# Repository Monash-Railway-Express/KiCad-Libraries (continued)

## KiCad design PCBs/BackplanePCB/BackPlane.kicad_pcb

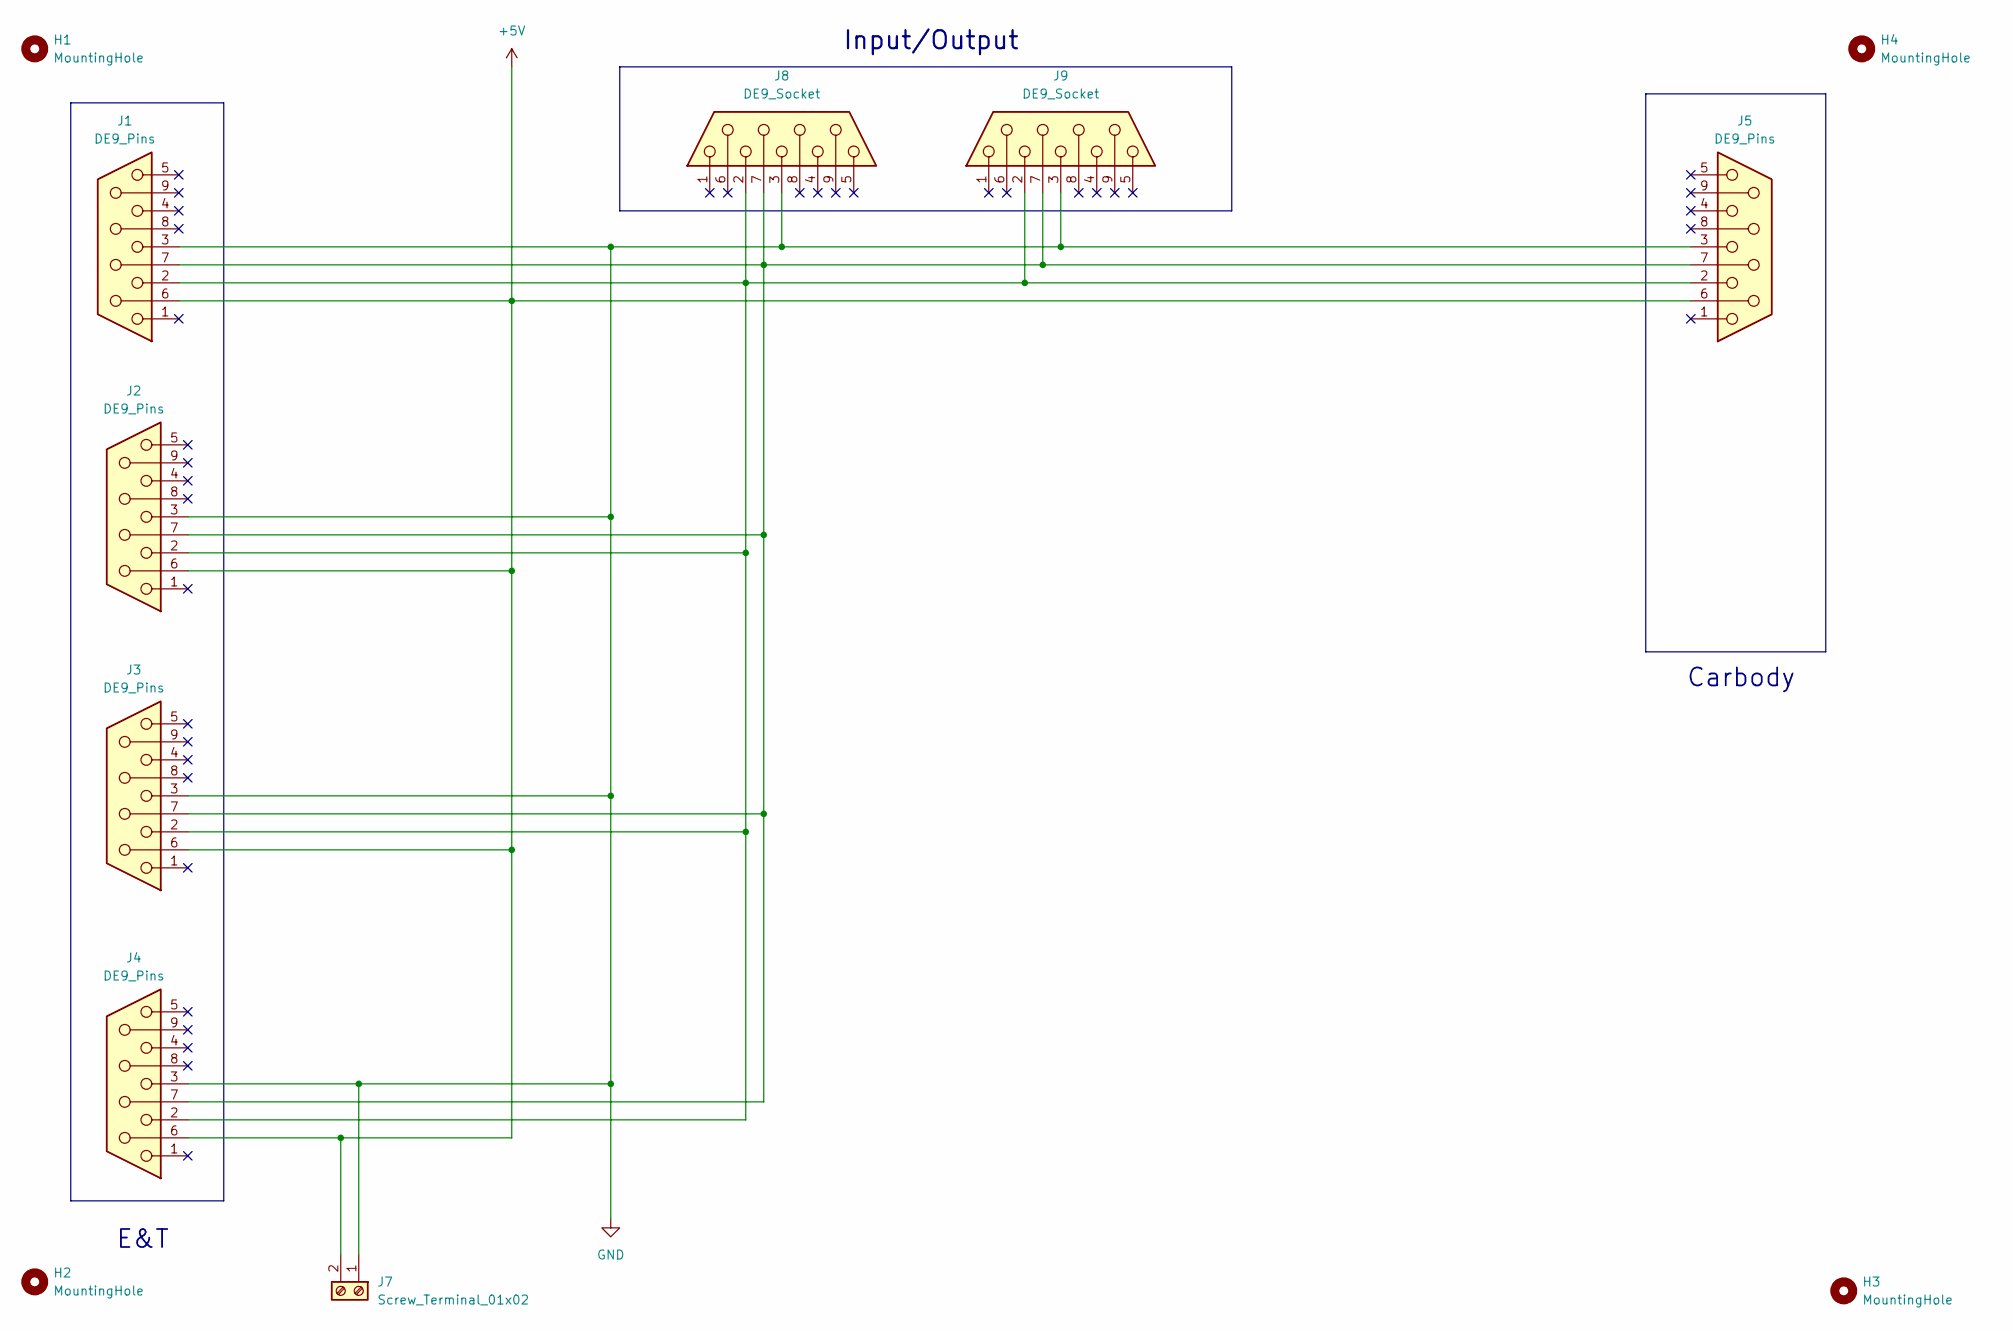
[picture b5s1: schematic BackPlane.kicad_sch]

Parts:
H1, H2, H3, H4: MountingHole; MountingHole_5.3mm_M5_ISO14580
J1, J2, J3, J4, J5: DE9_Pins; DSUB-9_Socket_Vertical_P2.77x2.84mm_MountingHoles
J7: Screw_Terminal_01x02; TerminalBlock_TE_282834-2_1x02_P2.54mm_Horizontal
J8, J9: DE9_Socket; CONN_2301844-1_TEC

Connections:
+5V: J1.6, J2.6, J3.6, J4.6, J5.6, J7.2
GND: J1.3, J2.3, J3.3, J4.3, J5.3, J7.1, J8.3, J9.3
unnamed: J1.2, J2.2, J3.2, J4.2, J5.2, J8.2, J9.2
unnamed: J1.7, J2.7, J3.7, J4.7, J5.7, J8.7, J9.7

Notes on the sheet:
Input/Output
E&T
Carbody

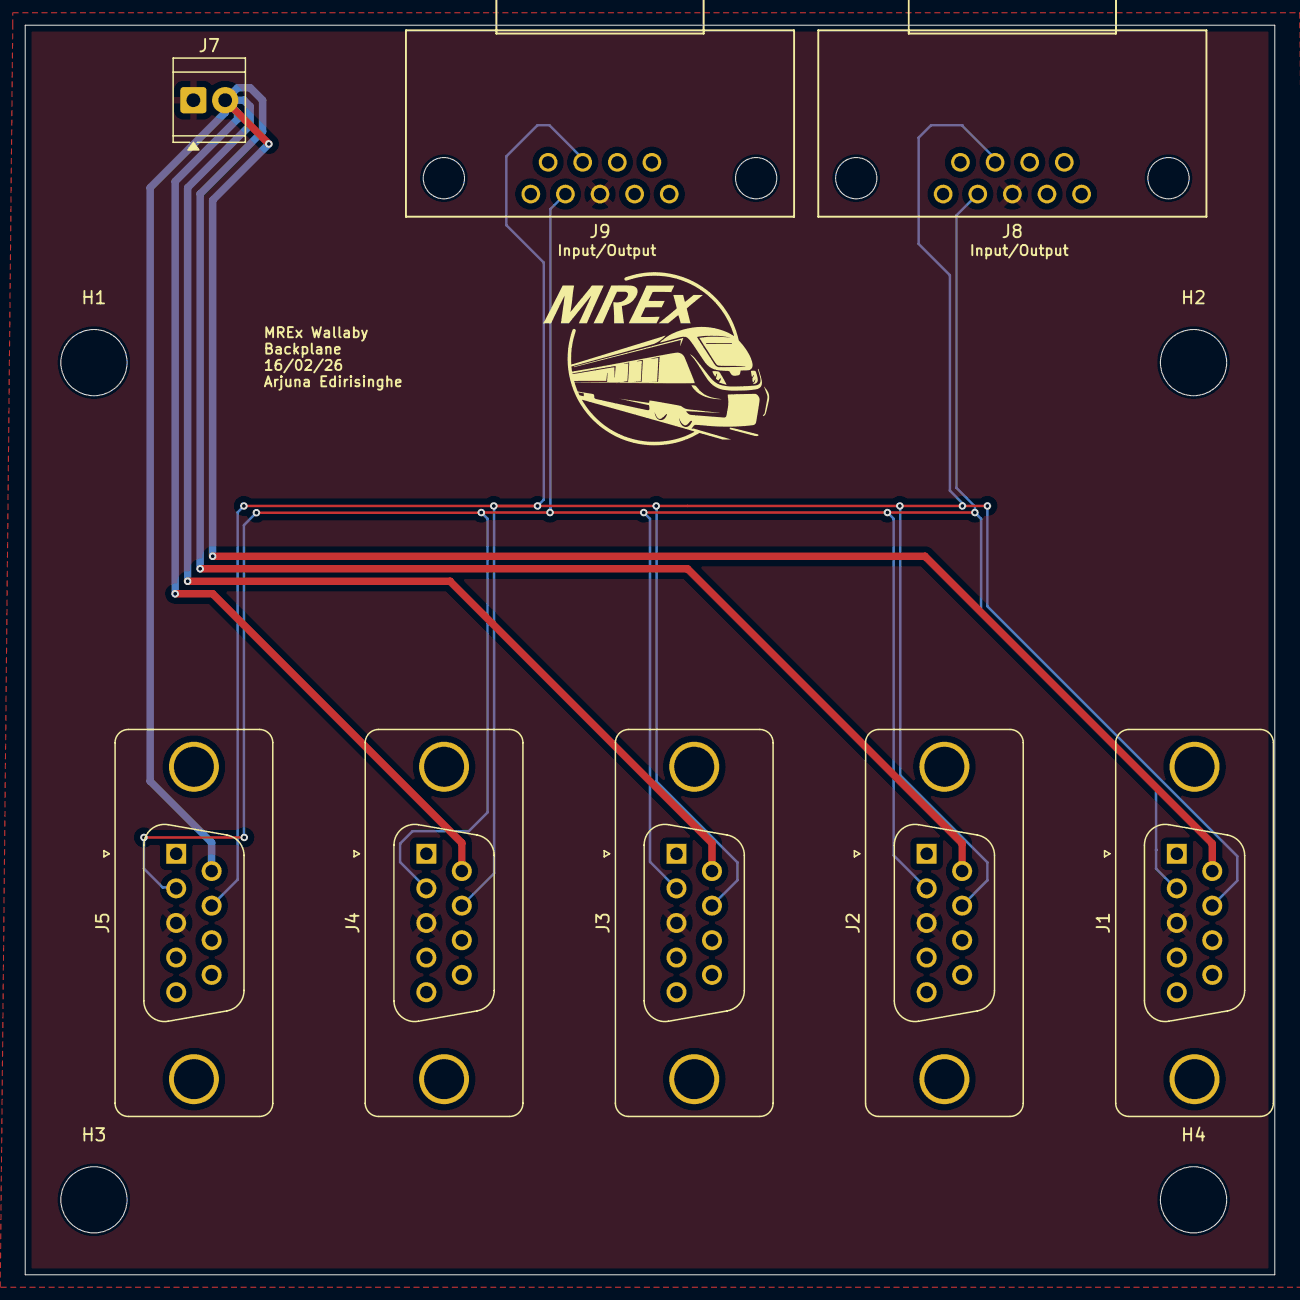
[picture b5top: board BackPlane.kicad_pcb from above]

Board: 2 copper layers, 100.0 x 100.0 mm, 12 parts (0 on the bottom side), 4 nets.

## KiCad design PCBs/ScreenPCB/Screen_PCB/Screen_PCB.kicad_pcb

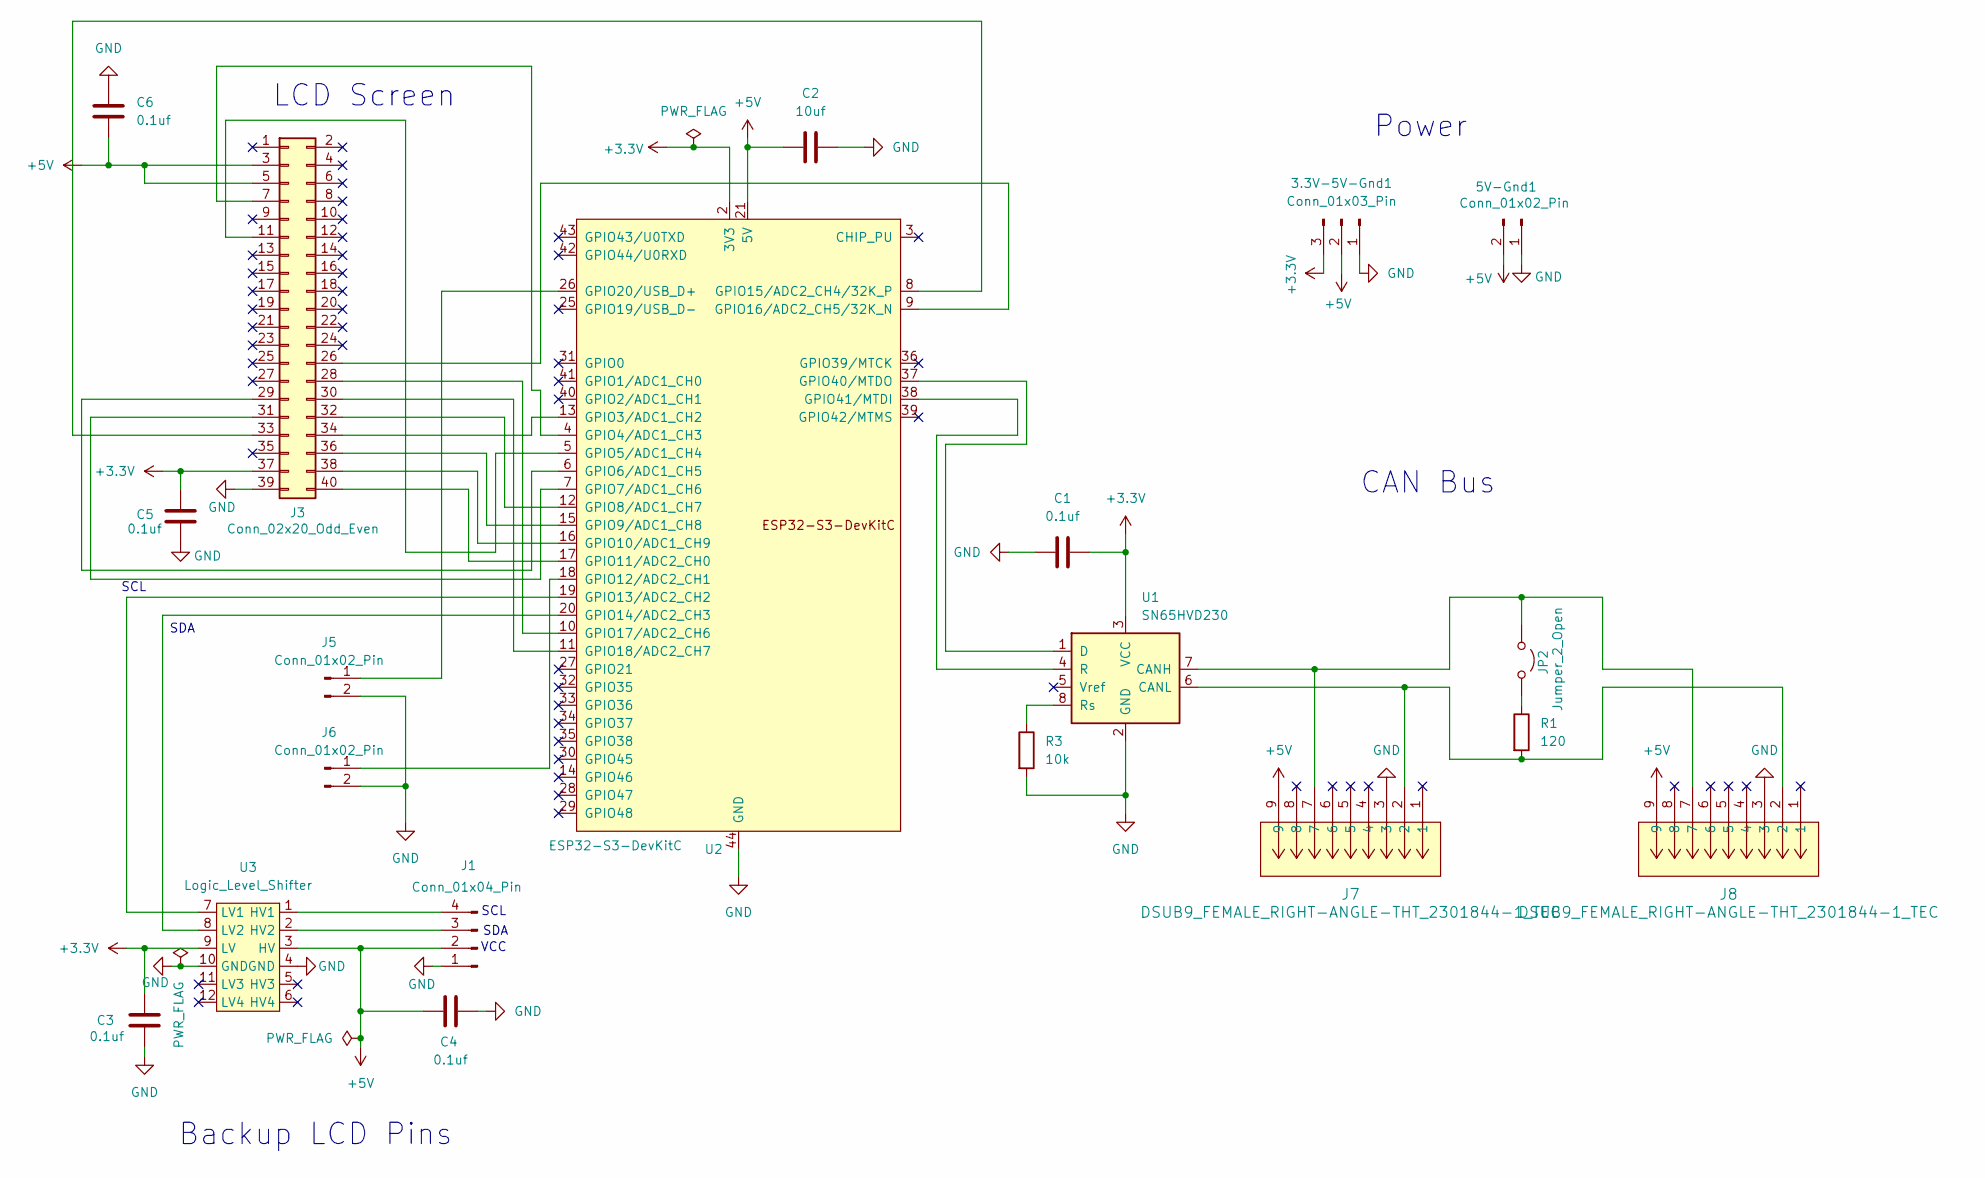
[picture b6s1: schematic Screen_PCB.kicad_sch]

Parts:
3.3V-5V-Gnd1: Conn_01x03_Pin; PinHeader_1x03_P2.54mm_Vertical
5V-Gnd1: Conn_01x02_Pin; PinHeader_1x02_P2.54mm_Vertical
C1, C3, C4, C5, C6: 0.1uf; C_0805_2012Metric
C2: 10uf; C_0805_2012Metric
J1: Conn_01x04_Pin; PinHeader_1x04_P2.54mm_Horizontal
J3: Conn_02x20_Odd_Even; IDC-Header_2x20_P2.54mm_Vertical
J5, J6: Conn_01x02_Pin; PinHeader_1x02_P2.54mm_Horizontal
J7, J8: DSUB9_FEMALE_RIGHT-ANGLE-THT_2301844-1_TEC
JP2: Jumper_2_Open; PinHeader_1x02_P2.54mm_Vertical
R1: 120; R_Axial_DIN0207_L6.3mm_D2.5mm_P7.62mm_Horizontal
R3: 10k; R_Axial_DIN0207_L6.3mm_D2.5mm_P7.62mm_Horizontal
U1: SN65HVD230; SOIC-8_3.9x4.9mm_P1.27mm
U2: ESP32-S3-DevKitC
U3: Logic_Level_Shifter; I2C_Logic_Shifter

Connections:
+3.3V: 3.3V-5V-Gnd1.3, C1.2, C3.1, C5.2, J3.37, U1.3 (VCC), U2.1 (3V3), U2.2 (3V3), U3.9 (LV); also elsewhere on the board
+5V: 3.3V-5V-Gnd1.2, 5V-Gnd1.2, C2.2, C4.1, C6.2, J1.2, J3.3, J3.5, J7.9, J8.9, U2.21 (5V), U3.3 (HV); also elsewhere on the board
GND: 3.3V-5V-Gnd1.1, 5V-Gnd1.1, C1.1, C2.1, C3.2, C4.2, C5.1, C6.1, J1.1, J3.39, J5.2, J6.2, J7.3, J8.3, R3.2, U1.2 (GND), U2.22 (GND), U2.23 (GND), U2.24 (GND), U2.44 (GND), U3.4 (GND), U3.10 (GND); also elsewhere on the board
unnamed: J1.3, U3.2 (HV2)
unnamed: J1.4, U3.1 (HV1)
unnamed: J3.7, U2.4 (GPIO4/ADC1_CH3)
unnamed: J3.11, U2.5 (GPIO5/ADC1_CH4)
unnamed: J3.26, U2.9 (GPIO16/ADC2_CH5/32K_N)
unnamed: J3.28, U2.10 (GPIO17/ADC2_CH6)
unnamed: J3.29, U2.6 (GPIO6/ADC1_CH5)
unnamed: J3.30, U2.11 (GPIO18/ADC2_CH7)
unnamed: J3.31, U2.7 (GPIO7/ADC1_CH6)
unnamed: J3.32, U2.12 (GPIO8/ADC1_CH7)
unnamed: J3.33, U2.8 (GPIO15/ADC2_CH4/32K_P)
unnamed: J3.34, U2.13 (GPIO3/ADC1_CH2)
unnamed: J3.36, U2.15 (GPIO9/ADC1_CH8)
unnamed: J3.38, U2.16 (GPIO10/ADC1_CH9)
unnamed: J3.40, U2.17 (GPIO11/ADC2_CH0)
unnamed: J5.1, U2.26 (GPIO20/USB_D+)
unnamed: J6.1, U2.18 (GPIO12/ADC2_CH1)
unnamed: J7.7, J8.7, JP2.1 (A), U1.7 (CANH)
unnamed: JP2.2 (B), R1.1
unnamed: J7.2, J8.2, R1.2, U1.6 (CANL)
unnamed: U1.1 (D), U2.37 (GPIO40/MTDO)
unnamed: U1.4 (R), U2.38 (GPIO41/MTDI)
unnamed: R3.1, U1.8 (Rs)
unnamed: U2.19 (GPIO13/ADC2_CH2), U3.7 (LV1)
unnamed: U2.20 (GPIO14/ADC2_CH3), U3.8 (LV2)

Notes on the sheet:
SCL
Power
LCD Screen
SDA
VCC
SDA
CAN Bus
SCL
Backup LCD Pins

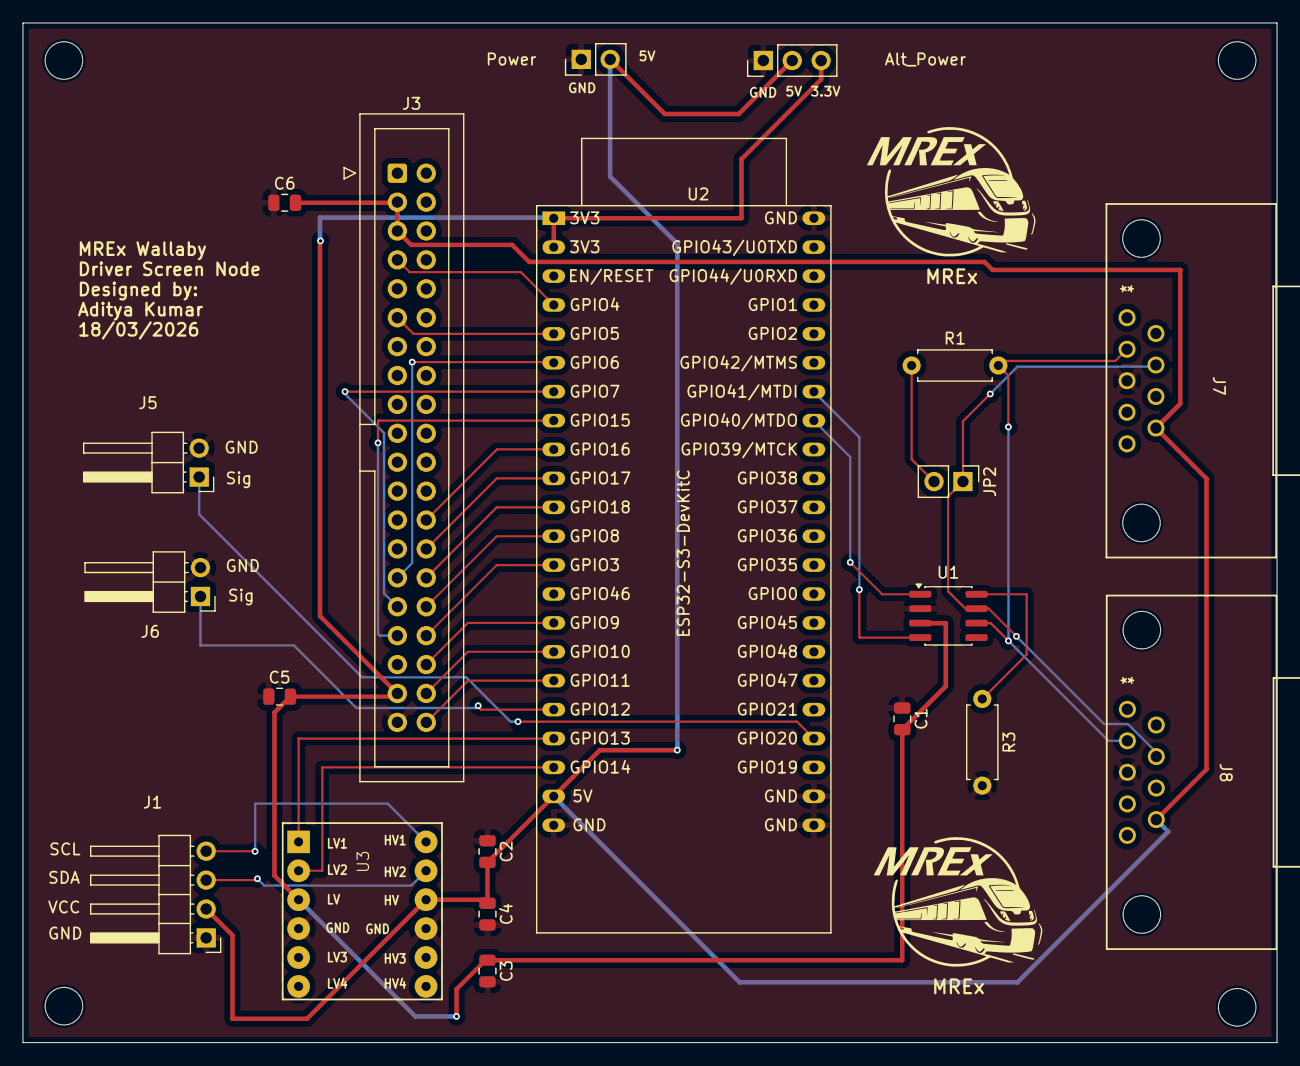
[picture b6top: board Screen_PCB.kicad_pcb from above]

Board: 2 copper layers, 110.2 x 89.6 mm, 22 parts (0 on the bottom side), 28 nets.

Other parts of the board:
Alt_Power: Conn_01x03_Pin; PinHeader_1x03_P2.54mm_Vertical
MREx: LOGO
MREx#2: LOGO
Power: Conn_01x02_Pin; PinHeader_1x02_P2.54mm_Vertical

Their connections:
+3.3V: Alt_Power.3; also elsewhere on the board
+5V: Alt_Power.2, Power.2; also elsewhere on the board
GND: Alt_Power.1, Power.1; also elsewhere on the board

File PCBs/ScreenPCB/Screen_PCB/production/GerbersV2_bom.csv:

Designator,Footprint,Quantity,Value,LCSC Part #
"_4, _3, _2, ",,4,,
BACKUP_SCREEN,PinHeader_1x04_P2.54mm_Horizontal,1,Conn_01x04_Pin,
"C1, C3, C4, C5, C6",0805,5,0.1uf,
C2,0805,1,10uf,
GND-5V,PinHeader_1x02_P2.54mm_Vertical,1,Conn_01x02_Pin,
GND-5V-3.3V,PinHeader_1x03_P2.54mm_Vertical,1,Conn_01x03_Pin,
J3,IDC-Header_2x20_P2.54mm_Vertical,1,Conn_02x20_Odd_Even,
"J7, J8",DSUB9_FEMALE_RIGHT-ANGLE-THT_2301844-1_TEC,2,DSUB9_FEMALE_RIGHT-ANGLE-THT_2301844-1_TEC,
JP2,PinHeader_1x02_P2.54mm_Vertical,1,Jumper_2_Open,
"PUSH_1, PUSH_2",PinHeader_1x02_P2.54mm_Horizontal,2,Conn_01x02_Pin,
R1,R_Axial_DIN0207_L6.3mm_D2.5mm_P7.62mm_Horizontal,1,120,
R3,R_Axial_DIN0207_L6.3mm_D2.5mm_P7.62mm_Horizontal,1,10k,
U1,SOIC-8_3.9x4.9mm_P1.27mm,1,SN65HVD230,
U2,ESP32-S3-DevKitC,1,ESP32-S3-DevKitC,
U3,I2C_Logic_Shifter,1,Logic_Level_Shifter,

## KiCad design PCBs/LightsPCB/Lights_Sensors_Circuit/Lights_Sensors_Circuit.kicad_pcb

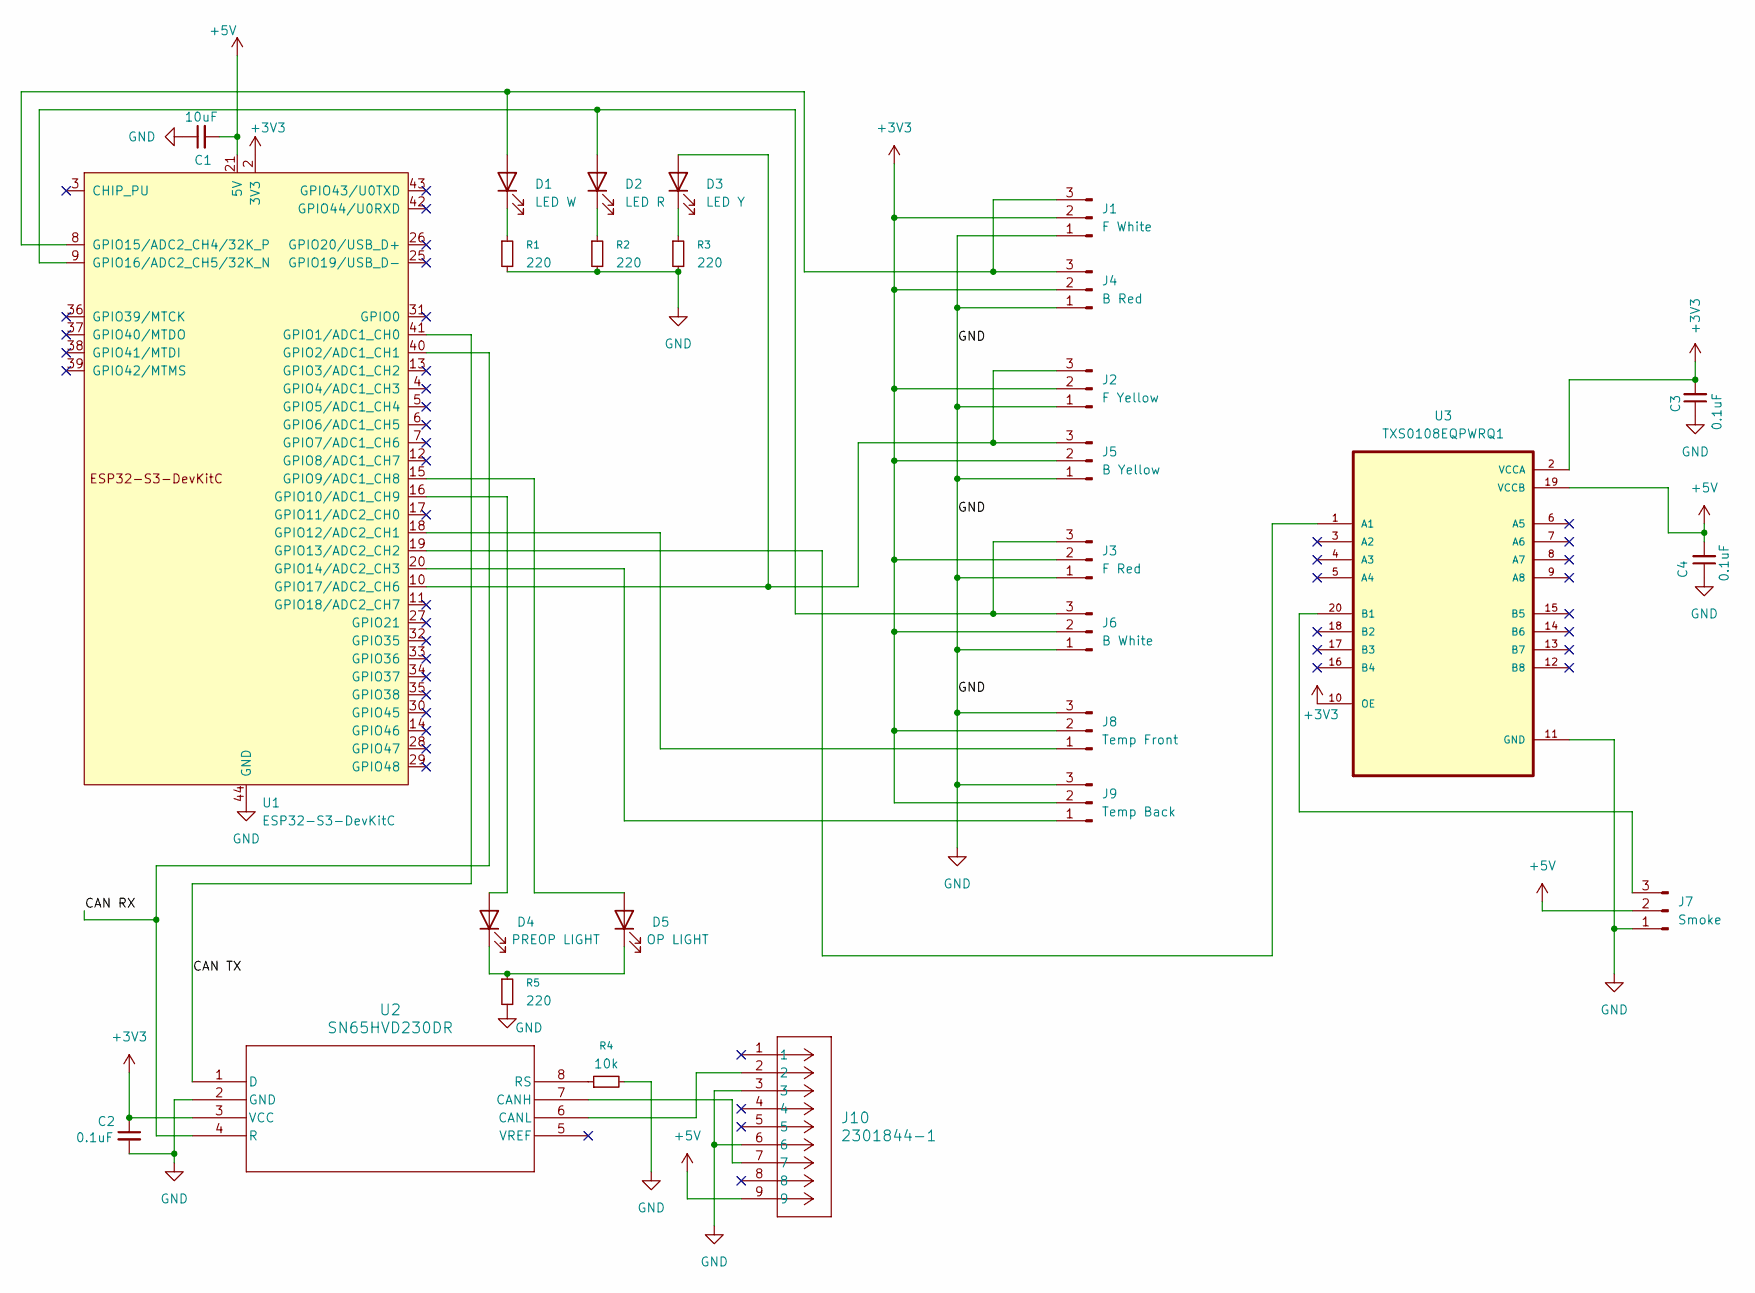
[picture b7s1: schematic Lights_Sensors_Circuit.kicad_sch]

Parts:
C1: 10uF; C_0805_2012Metric
C2, C3, C4: 0.1uF; C_0603_1608Metric
D1: LED W; LED_D5.0mm
D2: LED R; LED_D5.0mm
D3: LED Y; LED_D5.0mm
D4: PREOP LIGHT; LED_D5.0mm
D5: OP LIGHT; LED_D5.0mm
J1: F White; PinHeader_1x03_P2.54mm_Horizontal
J2: F Yellow; PinHeader_1x03_P2.54mm_Horizontal
J3: F Red; PinHeader_1x03_P2.54mm_Horizontal
J4: B Red; PinHeader_1x03_P2.54mm_Horizontal
J5: B Yellow; PinHeader_1x03_P2.54mm_Horizontal
J6: B White; PinHeader_1x03_P2.54mm_Horizontal
J7: Smoke; PinHeader_1x03_P2.54mm_Horizontal
J8: Temp Front; PinHeader_1x03_P2.54mm_Horizontal
J9: Temp Back; PinHeader_1x03_P2.54mm_Horizontal
J10: 2301844-1; CONN_2301844-1_TEC
R1, R2, R3, R5: 220; R_0603_1608Metric
R4: 10k; R_0603_1608Metric
U1: ESP32-S3-DevKitC
U2: SN65HVD230DR; D8
U3: TXS0108EQPWRQ1; SOP65P640X120-20N

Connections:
+3V3: C2.1, C3.2, J1.2, J2.2, J3.2, J4.2, J5.2, J6.2, J8.2, J9.2, U1.1 (3V3), U1.2 (3V3), U2.3 (VCC), U3.2 (VCCA), U3.10 (OE)
+5V: C1.2, C4.2, J7.2, J10.9, U1.21 (5V), U3.19 (VCCB)
/CAN RX: U1.40 (GPIO2/ADC1_CH1), U2.4 (R)
/CAN TX: U1.41 (GPIO1/ADC1_CH0), U2.1 (D)
GND: C1.1, C2.2, C3.1, C4.1, J1.1, J2.1, J3.1, J4.1, J5.1, J6.1, J7.1, J8.3, J9.3, J10.3, J10.6, R1.2, R2.2, R3.2, R4.2, R5.2, U1.22 (GND), U1.23 (GND), U1.24 (GND), U1.44 (GND), U2.2 (GND), U3.11 (GND)
unnamed: D1.2 (A), J1.3, J4.3, U1.8 (GPIO15/ADC2_CH4/32K_P)
unnamed: D1.1 (K), R1.1
unnamed: D2.2 (A), J3.3, J6.3, U1.9 (GPIO16/ADC2_CH5/32K_N)
unnamed: D2.1 (K), R2.1
unnamed: D3.2 (A), J2.3, J5.3, U1.10 (GPIO17/ADC2_CH6)
unnamed: D3.1 (K), R3.1
unnamed: D4.2 (A), U1.16 (GPIO10/ADC1_CH9)
unnamed: D4.1 (K), D5.1 (K), R5.1
unnamed: D5.2 (A), U1.15 (GPIO9/ADC1_CH8)
unnamed: J7.3, U3.20 (B1)
unnamed: J8.1, U1.18 (GPIO12/ADC2_CH1)
unnamed: J9.1, U1.20 (GPIO14/ADC2_CH3)
unnamed: U1.19 (GPIO13/ADC2_CH2), U3.1 (A1)
unnamed: J10.7, U2.7 (CANH)
unnamed: J10.2, U2.6 (CANL)
unnamed: R4.1, U2.8 (RS)

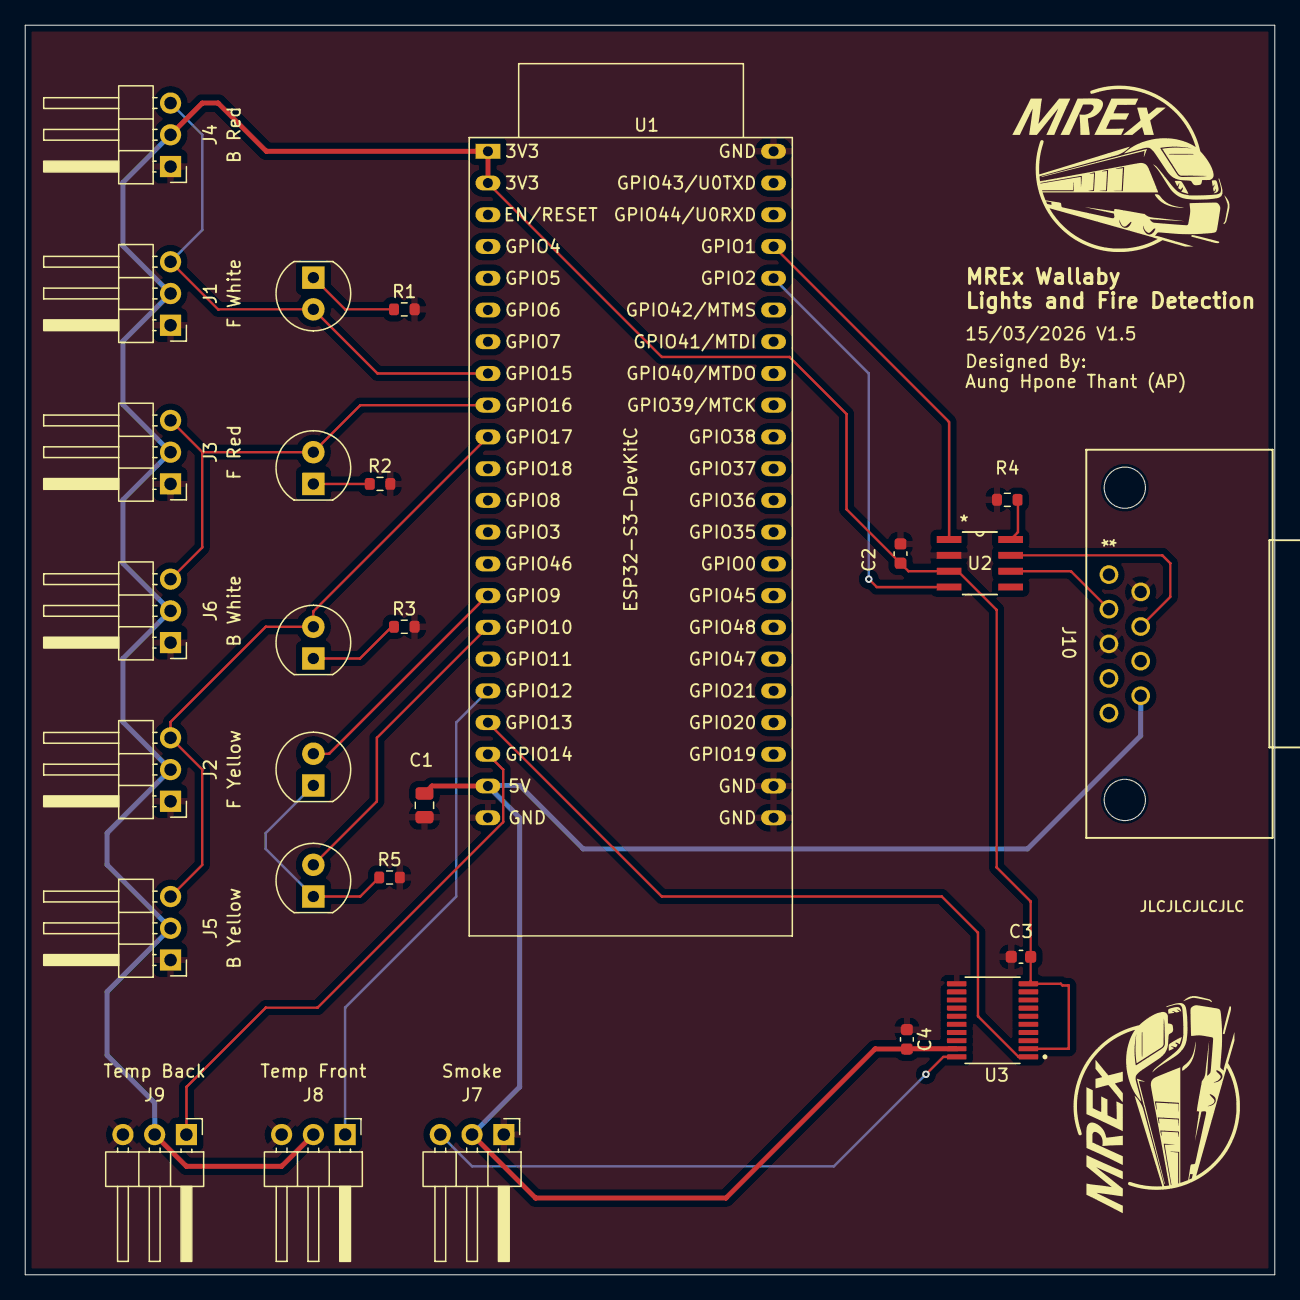
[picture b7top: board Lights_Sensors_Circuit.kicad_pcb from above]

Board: 2 copper layers, 100.0 x 100.0 mm, 27 parts (0 on the bottom side), 21 nets.

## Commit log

2026-02-15 footprints library added
2026-02-15 Symbol library added
2026-03-18 Change to KiCad-files
2026-03-18 Added screen pcb project
2026-03-18 Added driver controls kicad project
2026-03-18 Deleted DriverControls_Gerbers.zip
2026-03-18 Adding lights pcb
2026-03-19 upload gerbers
2026-03-29 Upload kicad files for shunt pcb
2026-04-18 Added Backplane PCB Kicad Files
2026-04-20 driver controls
2026-04-21 added autstop pcb
2026-04-23 Create folder for Horn version 2_1
2026-04-23 Added gerber files
2026-04-23 Added KICAD files
2026-04-27 Move old gerbers to a new folder. Latest version as of now is 2.1
2026-04-29 Updated kicad project files for horn
2026-04-29 Deleted conflicting old backups.
2026-04-29 Horn now uses DAC_R output instead of SPK1 and SPK2
    Initially the amp was hooked to SPK1 and SPK2 on the DFPlayer. These pins are actually connected to another onboard amplifier, which may have been damaging our larger amp.
2026-04-29 DFPlayer DAC_R outputs
2026-04-29 added driver controls v2
2026-04-29 Revert "added driver controls v2"
    This reverts commit c73e8f860f70517a898f0b3e351800c05ab551df.
2026-04-29 Reapply "added driver controls v2"
    This reverts commit d70487c3c1110107dce6cdfc2b36a156bfb5c696.
